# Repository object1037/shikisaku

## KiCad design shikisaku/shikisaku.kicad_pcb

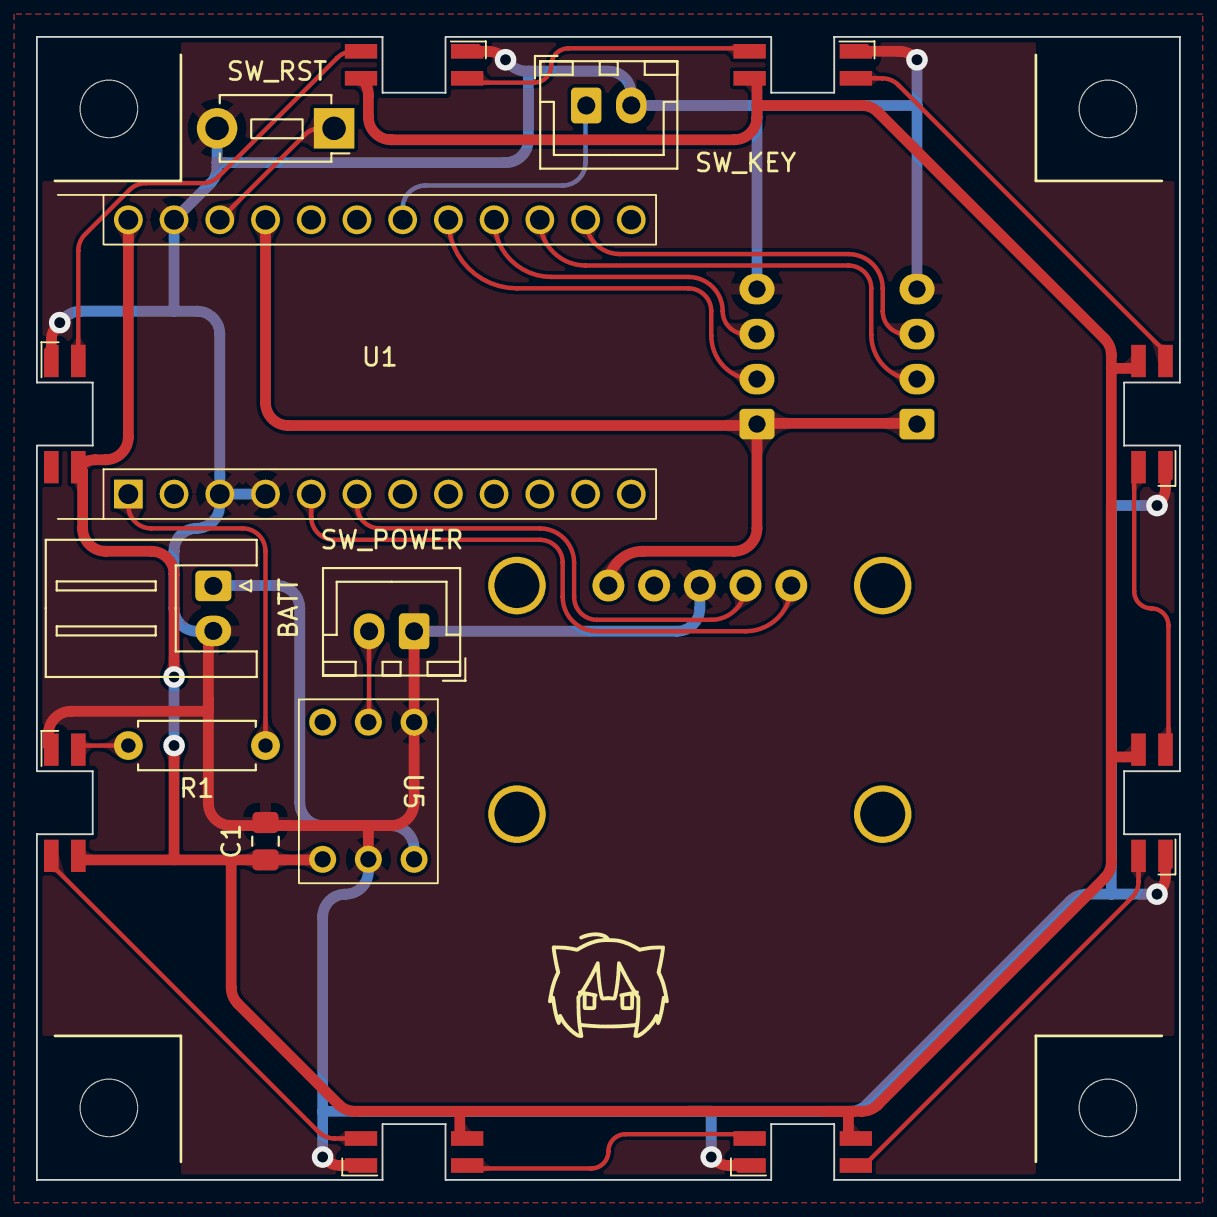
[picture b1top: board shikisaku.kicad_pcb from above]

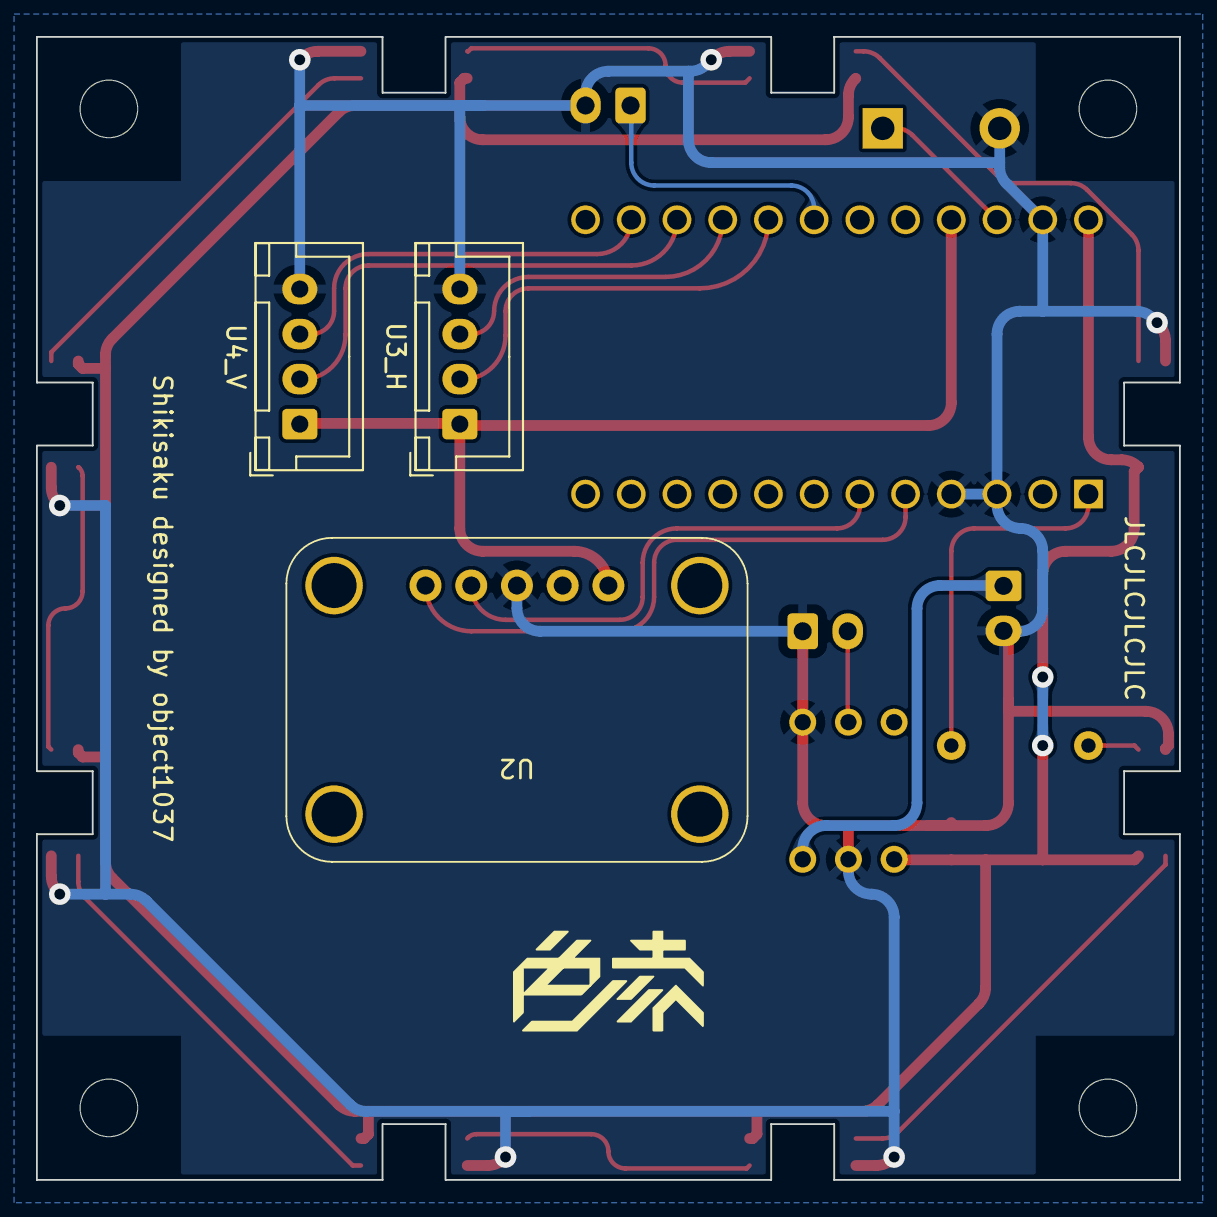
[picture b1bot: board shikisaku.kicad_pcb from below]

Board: 2 copper layers, 63.5 x 63.5 mm, 23 parts (11 on the bottom side), 22 nets.

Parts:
BATT: 3.6V; JST_XH_S2B-XH-A_1x02_P2.50mm_Horizontal
C1: 4.7u; C_0805_2012Metric_Pad1.18x1.45mm_HandSolder
D1, D2, D3, D4, D5, D6, D7, D8: SK6812MINI-E; LED_SK6812MINI-E
H1, H2, H3, H4: MountingHole; MountingHole_3.2mm_M3
R1: 220; R_Axial_DIN0207_L6.3mm_D2.5mm_P7.62mm_Horizontal
SW_KEY: SW_Push; JST_XH_B2B-XH-A_1x02_P2.50mm_Vertical
SW_POWER: SW_SPST; JST_XH_B2B-XH-A_1x02_P2.50mm_Vertical
SW_RST: SW_Reset; SW_PUSH_1P1T_6x3.5mm_H4.3_APEM_MJTP1243
U1: ProMicro; ProMicro-EnforcedTop
U2: MMC5603
U3_H, U4_V: HC-SR04; JST_XH_B4B-XH-A_1x04_P2.50mm_Vertical
U5: XCL103

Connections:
+5V: C1.1, D1.1 (VDD), D2.1 (VDD), D3.1 (VDD), D4.1 (VDD), D5.1 (VDD), D6.1 (VDD), D7.1 (VDD), D8.1 (VDD), U1.24 (RAW), U5.4 (OUT)
+BATT: BATT.1 (+), U5.6 (IN)
ECHO_H: U1.16 (B1), U3_H.3 (Echo)
ECHO_V: U1.14 (B2), U4_V.3 (Echo)
GND: BATT.2 (-), C1.2, D1.3 (GND), D2.3 (GND), D3.3 (GND), D4.3 (GND), D5.3 (GND), D6.3 (GND), D7.3 (GND), D8.3 (GND), SW_KEY.2, SW_POWER.1 (A), SW_RST.2, U1.3 (GND), U1.4 (GND), U1.23 (GND), U2.3 (GND), U3_H.4 (GND), U4_V.4 (GND), U5.1 (GND), U5.5 (GND)
KEY1: SW_KEY.1, U1.18 (F6)
LED: R1.1, U1.1 (TX)
unnamed: D1.4 (DIN), R1.2
unnamed: D1.2 (DOUT), D2.4 (DIN)
unnamed: D2.2 (DOUT), D3.4 (DIN)
unnamed: D3.2 (DOUT), D4.4 (DIN)
unnamed: D4.2 (DOUT), D5.4 (DIN)
unnamed: D5.2 (DOUT), D6.4 (DIN)
unnamed: D6.2 (DOUT), D7.4 (DIN)
unnamed: D7.2 (DOUT), D8.4 (DIN)
unnamed: SW_POWER.2 (B), U5.2 (EN)
RESET: SW_RST.1, U1.22 (RST)
SCL: U1.6 (SCL), U2.4 (SCL)
SDA: U1.5 (SDA), U2.5 (SDA)
TRIG_H: U1.17 (F7), U3_H.2 (Trig)
TRIG_V: U1.15 (B3), U4_V.2 (Trig)
VCC: U1.21 (VCC), U2.1 (VCC), U3_H.1 (VCC), U4_V.1 (VCC)

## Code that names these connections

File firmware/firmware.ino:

#include <Adafruit_MMC56x3.h>
#include <Adafruit_NeoPixel.h>
#include <avr/power.h>
#include <Keyboard.h>
#include <EEPROM.h>

// #define DEBUG

const int TRIG_H = 18;
const int ECHO_H = 15;
const int TRIG_V = 14;
const int ECHO_V = 16;
const int LED = 1;
const int NUMLEDS = 8;
const int KEY = 19;

const int DIST_H_MIN = 15;
const int DIST_H_MAX = 25;
const int DIST_V_MIN = 20;
const int DIST_V_MAX = 40;

const int HOLD_ADDR = 0;
const int COLOR_ADDR = HOLD_ADDR + sizeof(bool);

typedef struct {
  double L;
  double C;
  double h;
} LCh_t;
typedef struct {
  double r;
  double g;
  double b;
} RGB_t;

const double hard_iron[3] = {28.38, -42.28, 71.21};
const double soft_iron[3][3] = {
  {0.975, 0.01, 0.003},
  {0.01, 1.015, -0.039},
  {0.003, -0.039, 1.012}
};

Adafruit_MMC5603 mag = Adafruit_MMC5603(12345);
sensors_event_t mag_event;

Adafruit_NeoPixel pixels(NUMLEDS, LED, NEO_GRB + NEO_KHZ800);

double dist_h_lp = 0;
double dist_v_lp = 0;

RGB_t prev_color = {.r = 0, .g = 0, .b = 0};
RGB_t cur_color = {.r = 0, .g = 0, .b = 0};
int grad_idx = 0;

unsigned long prev_time = 0;
unsigned long prev_micros = 0;
unsigned long loop_interval = 200;

bool is_holding;
RGB_t hold_color;

double lowpass(const double sample, const double prev, const double rc) {
  return sample - rc * (sample - prev);
}

double measure_distance(const int TRIG, const int ECHO, const double temp) {
  digitalWrite(TRIG, LOW);
  delayMicroseconds(2);
  digitalWrite(TRIG, HIGH);
  delayMicroseconds(10);
  digitalWrite(TRIG, LOW);
  double duration = pulseIn(ECHO, HIGH);
  double velocity = 331.45 + 0.61 * temp;

  if (duration > 0) {
    double distance = duration / 2 / 1000000 * velocity * 100;
    return distance;
  }
  return -1;
}

double dist_percentage(const double dist, const int d_min, const int d_max) {
  int range = d_max - d_min;
  return (dist - d_min) / range;
}

void calibrate_mag(sensors_event_t* mag_event, double* x, double* y) {
  double mag_data[] = {
    mag_event->magnetic.x,
    mag_event->magnetic.y,
    mag_event->magnetic.z
  };
  double hi_cal[3];

  for (int i = 0; i < 3; i++) {
    hi_cal[i] = mag_data[i] - hard_iron[i];
  }
  for (int i = 0; i < 3; i++) {
    mag_data[i] = soft_iron[i][0] * hi_cal[0] + soft_iron[i][1] * hi_cal[1] + soft_iron[i][2] * hi_cal[2];
  }

  *x = mag_data[0];
  *y = mag_data[1];

  return;
}

double get_heading(const double x, const double y) {
  double heading = -1 * atan2(x, y);
  if (heading < 0) {
    heading += 2 * M_PI;
  }
  return heading;
}

double gamma_correction(const double c) {
  double abs = abs(c);
  int sign = 1;
  if (c < 0) {
    sign = -1;
  }
  if (abs <= 0.0031308) {
    return c * 12.92;
  }

  return sign * (1.055 * pow(abs, 1.0 / 2.4) - 0.055);
}

RGB_t oklch_to_rgb(const LCh_t* lch) {
  double a = lch->C * cos(lch->h);
  double b = lch->C * sin(lch->h);

  double l_ = lch->L + 0.3963377774f * a + 0.2158037573f * b;
  double m_ = lch->L - 0.1055613458f * a - 0.0638541728f * b;
  double s_ = lch->L - 0.0894841775f * a - 1.2914855480f * b;

  double l = l_*l_*l_;
  double m = m_*m_*m_;
  double s = s_*s_*s_;

  return {
    .r = +4.0767416621f * l - 3.3077115913f * m + 0.2309699292f * s,
    .g = -1.2684380046f * l + 2.6097574011f * m - 0.3413193965f * s,
    .b = -0.0041960863f * l - 0.7034186147f * m + 1.7076147010f * s
  };
}

bool is_valid(const RGB_t *rgb) {
  bool ans = true;
  if (rgb->r < 0 || rgb->r > 1) ans = false;
  if (rgb->g < 0 || rgb->g > 1) ans = false;
  if (rgb->b < 0 || rgb->b > 1) ans = false;
  return ans;
}

int to_valid(const double c) {
  return constrain(int(255 * c), 0, 255);
}

double nth_div(const double prev, const double cur, const int idx, const int n) {
  double ans = prev + (cur - prev) / (n-1) * idx;
  return ans;
}

void light_LED(const RGB_t *prev, RGB_t *cur, const int idx) {
  for (int j = 0; j < NUMLEDS; j++) {
    pixels.setPixelColor(j, pixels.Color(
      to_valid(nth_div(prev->r, cur->r, idx, 10)),
      to_valid(nth_div(prev->g, cur->g, idx, 10)),
      to_valid(nth_div(prev->b, cur->b, idx, 10))
    ));
  }
  pixels.show();
}

void light_LED_delay(const RGB_t *prev, const RGB_t *cur) {
  for (int i = 0; i < 10; i++) {
    for (int j = 0; j < NUMLEDS; j++) {
      pixels.setPixelColor(j, pixels.Color(
        to_valid(nth_div(prev->r, cur->r, i, 10)),
        to_valid(nth_div(prev->g, cur->g, i, 10)),
        to_valid(nth_div(prev->b, cur->b, i, 10))
      ));
    }
    pixels.show();
    delay(15);
  }
}

void print_hex(const RGB_t *rgb) {
  long R = to_valid(gamma_correction(rgb->r));
  long G = to_valid(gamma_correction(rgb->g));
  long B = to_valid(gamma_correction(rgb->b));
  long RGB = (R << 16L) | (G << 8L) | B;
  String hex = String("#" + String(RGB, HEX));
  Keyboard.print(hex);
}

void setup() {
  pinMode(TRIG_H, OUTPUT);
  pinMode(TRIG_V, OUTPUT);
  pinMode(ECHO_H, INPUT);
  pinMode(ECHO_V, INPUT);
  pinMode(KEY, INPUT_PULLUP);

  Keyboard.begin();

  EEPROM.get(HOLD_ADDR, is_holding);
  EEPROM.get(COLOR_ADDR, hold_color);

  if (is_holding) {
    prev_color = hold_color;
    cur_color = hold_color;
  }

  pixels.begin();
  pixels.show();
  // pixels.setBrightness(75);

#ifdef DEBUG
  Serial.begin(9600);
#endif
  if (!mag.begin(MMC56X3_DEFAULT_ADDRESS, &Wire)) {
#ifdef DEBUG
    Serial.println(F("Could not find a magnetometer, check wiring!"));
#endif
    while(1) delay(10);
  }
  delay(100);

  mag.getEvent(&mag_event);
  
  delay(10);
}

void loop() {
  unsigned long cur_time = millis();
  if (is_holding || cur_time - prev_time < loop_interval) {
    if (is_holding) {
      light_LED(&hold_color, &hold_color, 9);
    } else {
      unsigned long cur_micros = micros();
      if (cur_micros - prev_micros >= 10000) {
        light_LED(&prev_color, &cur_color, grad_idx);
        grad_idx++;
        if (grad_idx >= 10) grad_idx = 9;
        prev_micros = cur_micros;
      }
    }
    if (digitalRead(KEY) == LOW) {
      bool holded = false;
      while (digitalRead(KEY) == LOW) {
        unsigned long next_time = millis();
        if (!holded && next_time - cur_time > 250) {
          holded = true;
          is_holding = !is_holding;
          hold_color = cur_color;
          EEPROM.put(HOLD_ADDR, is_holding);
          EEPROM.put(COLOR_ADDR, hold_color);
          const RGB_t black = {.r = 0, .g = 0, .b = 0};
          light_LED_delay(&hold_color, &black);
          light_LED_delay(&black, &hold_color);
        }
      }
      if (!holded) {
        print_hex(&cur_color);
      }
    }
    return;
  }
  prev_color = cur_color;

  mag.getEvent(&mag_event);
  double mag_x = 0;
  double mag_y = 0;
  calibrate_mag(&mag_event, &mag_x, &mag_y);

  double heading_rad = get_heading(mag_x, mag_y);
  
  double temp = mag.readTemperature();
  double dist_v_raw = measure_distance(TRIG_V, ECHO_V, temp);
  double dist_h_raw = measure_distance(TRIG_H, ECHO_H, temp);
  dist_h_lp = lowpass(constrain(dist_h_raw, DIST_H_MIN, DIST_H_MAX), dist_h_lp, 0.5);
  dist_v_lp = lowpass(constrain(dist_v_raw, DIST_V_MIN, DIST_V_MAX), dist_v_lp, 0.5);
  double h_perc = dist_percentage(dist_h_lp, DIST_H_MIN, DIST_H_MAX);
  double v_perc = dist_percentage(dist_v_lp, DIST_V_MIN, DIST_V_MAX);

  LCh_t lch = {
    .L = v_perc,
    .C = 0.3 * h_perc,
    .h = heading_rad
  };
  cur_color = oklch_to_rgb(&lch);

  if (!is_valid(&cur_color)) {
    cur_color.r = 0;
    cur_color.g = 0;
    cur_color.b = 0;
  }

#ifdef DEBUG
  // Serial.print(F("Heading: "));
  Serial.print(prev_time); Serial.print("->");
  Serial.print(cur_time); Serial.print(" ");
  double heading_deg = heading_rad * 180 / M_PI;
  Serial.print(heading_deg); Serial.print(", ");
  Serial.print(temp); Serial.print(", ");

  // Serial.print(F(" Dist: "));
  Serial.print(dist_h_raw); Serial.print(", ");
  Serial.print(dist_h_lp); Serial.print(", ");
  Serial.print(dist_v_raw); Serial.print(", ");
  Serial.print(dist_v_lp); Serial.print(", ");

  Serial.print("lch(");
  Serial.print(lch.L, 5); Serial.print(", ");
  Serial.print(lch.C, 5); Serial.print(", ");
  Serial.print(lch.h * 180 / M_PI); Serial.print(") -> ");

  Serial.print("rgb(");
  Serial.print(255 * cur_color.r); Serial.print(", ");
  Serial.print(255 * cur_color.g); Serial.print(", ");
  Serial.print(255 * cur_color.b); Serial.print("), ");

  Serial.print("prev(");
  Serial.print(255 * prev_color.r); Serial.print(", ");
  Serial.print(255 * prev_color.g); Serial.print(", ");
  Serial.print(255 * prev_color.b); Serial.print(")");
  Serial.println();
#endif

  prev_time = cur_time;
  grad_idx = 0;
}

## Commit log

2023-11-15 add ignore file
2023-11-15 implement magnetometer calibration and LCh -> sRGB conversion
2023-11-18 apply lowpass filter to usonic sensor
2023-11-18 add motioncal sketch
2023-11-28 データ保存のため変更
2023-11-28 calculate RGB value from sensor inputs
2023-11-28 light LED
2023-11-28 add KiCad proj
2023-12-03 update schematic
2023-12-05 assign footprints
2023-12-05 layout footprints
2023-12-05 add mounting holes
2023-12-05 update footprint
2023-12-05 配線(仮)
2023-12-06 use SK6812MINI-E
2023-12-11 配線完了
2023-12-12 complete and output Gerber
2023-12-12 update ignore
2023-12-12 update edge cuts
2023-12-26 use neopixel
2024-01-17 finish acrylic design and firmware
2024-01-17 update firmware
2024-01-18 add README
2024-01-18 organize
